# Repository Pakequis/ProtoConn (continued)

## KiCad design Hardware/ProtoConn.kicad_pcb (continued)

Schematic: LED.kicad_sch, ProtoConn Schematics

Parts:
D3, D4, D5, D6, D7, D8, D9, D10: LED; LED_0603_1608Metric
J51: 01x02; PinHeader_1x02_P2.54mm_Vertical
J52: Conn_01x08; PinHeader_1x08_P2.54mm_Vertical
JP9: Jumper; PinHeader_1x02_P2.54mm_Vertical
R51, R52, R53, R54, R55, R56, R57, R58: 0603; R_0603_1608Metric_Pad0.98x0.95mm_HandSolder

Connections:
GNDREF: JP9.2 (B); also elsewhere on the board
unnamed: D3.2 (A), J52.1
unnamed: D3.1 (K), R51.2
unnamed: D4.2 (A), J52.2
unnamed: D4.1 (K), R52.1
unnamed: D5.2 (A), J52.3
unnamed: D5.1 (K), R53.1
unnamed: D6.2 (A), J52.4
unnamed: D6.1 (K), R54.2
unnamed: D7.2 (A), J52.5
unnamed: D7.1 (K), R55.1
unnamed: D8.2 (A), J52.6
unnamed: D8.1 (K), R56.1
unnamed: D9.2 (A), J52.7
unnamed: D9.1 (K), R57.2
unnamed: D10.2 (A), J52.8
unnamed: D10.1 (K), R58.1
unnamed: J51.1, J51.2, JP9.1 (A), R51.1, R52.2, R53.2, R54.1, R55.2, R56.2, R57.1, R58.2

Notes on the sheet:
Notes: 1. The LEDs are connected as common cathode. To switch to common anode, the LEDs need to be reversed.
Connect to board GND
LED

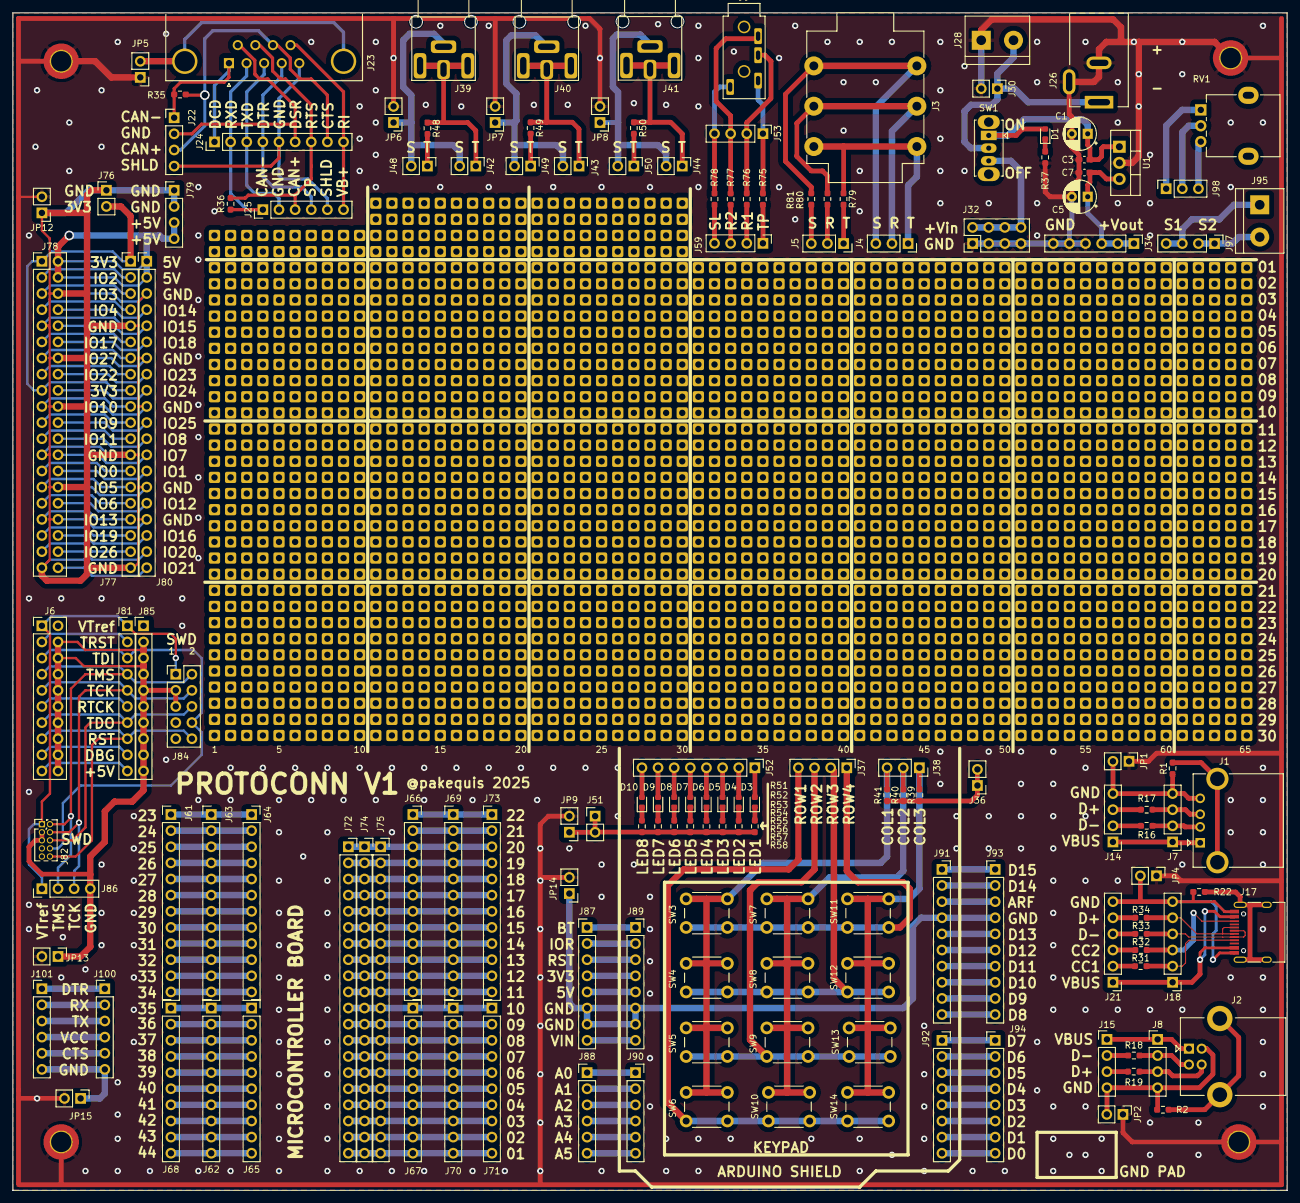
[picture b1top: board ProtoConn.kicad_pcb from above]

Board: 2 copper layers, 200.7 x 185.4 mm, 156 parts (0 on the bottom side), 216 nets.

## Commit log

2025-01-11 license file
2025-01-11 Full license
2025-01-11 first image
2025-03-30 full project
